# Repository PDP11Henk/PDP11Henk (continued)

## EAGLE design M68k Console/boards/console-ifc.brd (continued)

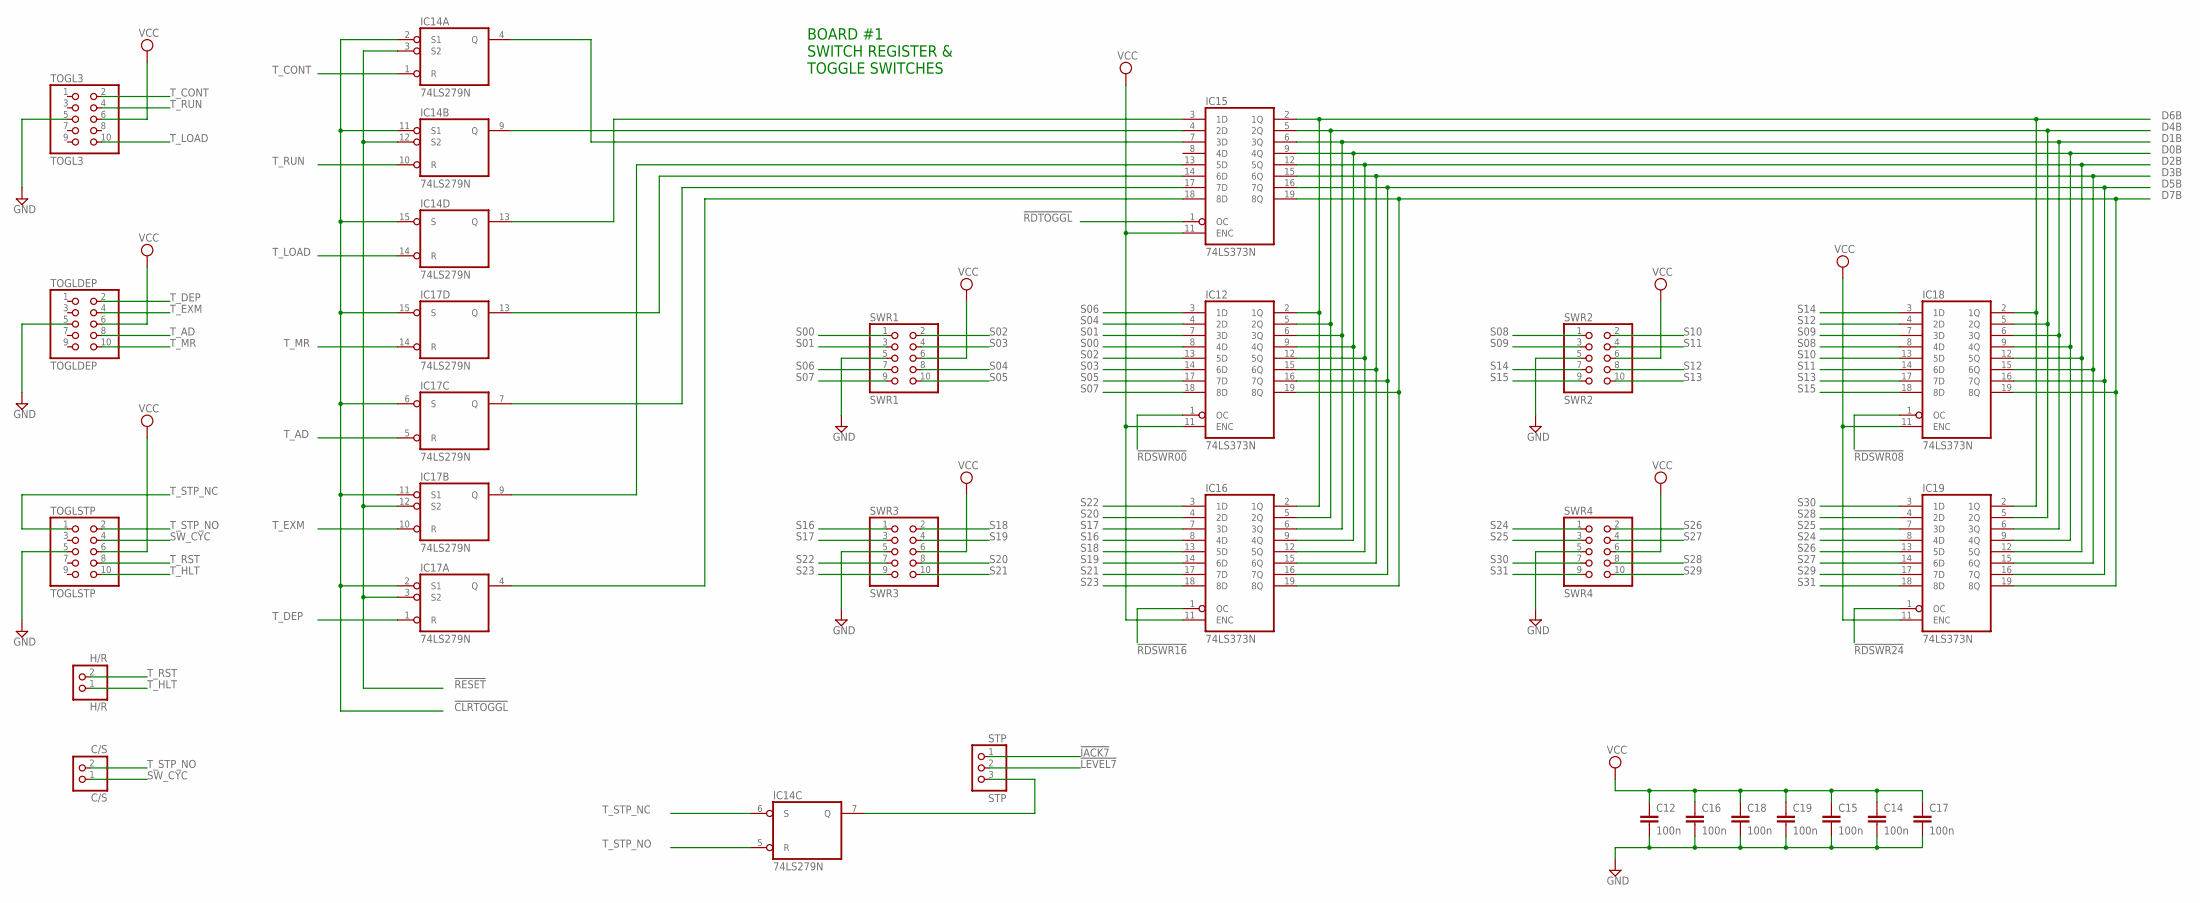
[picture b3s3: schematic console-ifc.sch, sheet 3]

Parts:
C12, C14, C15, C16, C17, C18, C19: 100n; C025-024X044
C/S: C/S; 1X02
H/R: H/R; 1X02
IC12, IC15, IC16, IC18, IC19: 74LS373N; DIL20
IC14, IC17: 74LS279N; DIL16
STP: STP; 1X03
SWR1: SWR1; 2X05
SWR2: SWR2; 2X05
SWR3: SWR3; 2X05
SWR4: SWR4; 2X05
TOGL3: TOGL3; 2X05
TOGLDEP: TOGLDEP; 2X05
TOGLSTP: TOGLSTP; 2X05

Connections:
!CLRTOGGL: IC14.2 (S1), IC14.11 (S1), IC14.15 (S), IC17.2 (S1), IC17.6 (S), IC17.11 (S1), IC17.15 (S); also elsewhere on the board
!IACK7: STP.1; also elsewhere on the board
!LEVEL7: STP.2; also elsewhere on the board
!RDSWR00: IC12.1 (OC); also elsewhere on the board
!RDSWR08: IC18.1 (OC); also elsewhere on the board
!RDSWR16: IC16.1 (OC); also elsewhere on the board
!RDSWR24: IC19.1 (OC); also elsewhere on the board
!RDTOGGL: IC15.1 (OC); also elsewhere on the board
!RESET: IC14.3 (S2), IC14.12 (S2), IC17.3 (S2), IC17.12 (S2); also elsewhere on the board
D0B: IC12.9 (4Q), IC15.9 (4Q), IC16.9 (4Q), IC18.9 (4Q), IC19.9 (4Q); also elsewhere on the board
D1B: IC12.6 (3Q), IC15.6 (3Q), IC16.6 (3Q), IC18.6 (3Q), IC19.6 (3Q); also elsewhere on the board
D2B: IC12.12 (5Q), IC15.12 (5Q), IC16.12 (5Q), IC18.12 (5Q), IC19.12 (5Q); also elsewhere on the board
D3B: IC12.15 (6Q), IC15.15 (6Q), IC16.15 (6Q), IC18.15 (6Q), IC19.15 (6Q); also elsewhere on the board
D4B: IC12.5 (2Q), IC15.5 (2Q), IC16.5 (2Q), IC18.5 (2Q), IC19.5 (2Q); also elsewhere on the board
D5B: IC12.16 (7Q), IC15.16 (7Q), IC16.16 (7Q), IC18.16 (7Q), IC19.16 (7Q); also elsewhere on the board
D6B: IC12.2 (1Q), IC15.2 (1Q), IC16.2 (1Q), IC18.2 (1Q), IC19.2 (1Q); also elsewhere on the board
D7B: IC12.19 (8Q), IC15.19 (8Q), IC16.19 (8Q), IC18.19 (8Q), IC19.19 (8Q); also elsewhere on the board
GND: C12.2, C14.2, C15.2, C16.2, C17.2, C18.2, C19.2, IC12.10 (GND), IC14.8 (GND), IC15.10 (GND), IC16.10 (GND), IC17.8 (GND), IC18.10 (GND), IC19.10 (GND), SWR1.5, SWR2.5, SWR3.5, SWR4.5, TOGL3.5, TOGLDEP.5, TOGLSTP.5; also elsewhere on the board
unnamed: IC15.18 (8D), IC17.4 (Q)
unnamed: IC14.7 (Q), STP.3
unnamed: IC15.17 (7D), IC17.7 (Q)
unnamed: IC15.14 (6D), IC17.13 (Q)
unnamed: IC15.13 (5D), IC17.9 (Q)
unnamed: IC14.13 (Q), IC15.3 (1D)
unnamed: IC14.9 (Q), IC15.4 (2D)
unnamed: IC14.4 (Q), IC15.7 (3D)
S00: IC12.8 (4D), SWR1.1
S01: IC12.7 (3D), SWR1.3
S02: IC12.13 (5D), SWR1.2
S03: IC12.14 (6D), SWR1.4
S04: IC12.4 (2D), SWR1.8
S05: IC12.17 (7D), SWR1.10
S06: IC12.3 (1D), SWR1.7
S07: IC12.18 (8D), SWR1.9
S08: IC18.8 (4D), SWR2.1
S09: IC18.7 (3D), SWR2.3
S10: IC18.13 (5D), SWR2.2
S11: IC18.14 (6D), SWR2.4
S12: IC18.4 (2D), SWR2.8
S13: IC18.17 (7D), SWR2.10
S14: IC18.3 (1D), SWR2.7
S15: IC18.18 (8D), SWR2.9
S16: IC16.8 (4D), SWR3.1
S17: IC16.7 (3D), SWR3.3
S18: IC16.13 (5D), SWR3.2
S19: IC16.14 (6D), SWR3.4
S20: IC16.4 (2D), SWR3.8
S21: IC16.17 (7D), SWR3.10
S22: IC16.3 (1D), SWR3.7
S23: IC16.18 (8D), SWR3.9
S24: IC19.8 (4D), SWR4.1
S25: IC19.7 (3D), SWR4.3
S26: IC19.13 (5D), SWR4.2
S27: IC19.14 (6D), SWR4.4
S28: IC19.4 (2D), SWR4.8
S29: IC19.17 (7D), SWR4.10
S30: IC19.3 (1D), SWR4.7
S31: IC19.18 (8D), SWR4.9
SW_CYC: C/S.1, TOGLSTP.4
T_AD: IC17.5 (R), TOGLDEP.8
T_CONT: IC14.1 (R), TOGL3.2
T_DEP: IC17.1 (R), TOGLDEP.2
T_EXM: IC17.10 (R), TOGLDEP.4
T_HLT: H/R.1, TOGLSTP.10
T_LOAD: IC14.14 (R), TOGL3.10
T_MR: IC17.14 (R), TOGLDEP.10
T_RST: H/R.2, TOGLSTP.8
T_RUN: IC14.10 (R), TOGL3.4
T_STP_NC: IC14.6 (S), TOGLSTP.1
T_STP_NO: C/S.2, IC14.5 (R), TOGLSTP.2
VCC: C12.1, C14.1, C15.1, C16.1, C17.1, C18.1, C19.1, IC12.11 (ENC), IC12.20 (VCC), IC14.16 (VCC), IC15.11 (ENC), IC15.20 (VCC), IC16.11 (ENC), IC16.20 (VCC), IC17.16 (VCC), IC18.11 (ENC), IC18.20 (VCC), IC19.11 (ENC), IC19.20 (VCC), SWR1.6, SWR2.6, SWR3.6, SWR4.6, TOGL3.6, TOGLDEP.6, TOGLSTP.6; also elsewhere on the board

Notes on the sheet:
BOARD #1 SWITCH REGISTER & TOGGLE SWITCHES

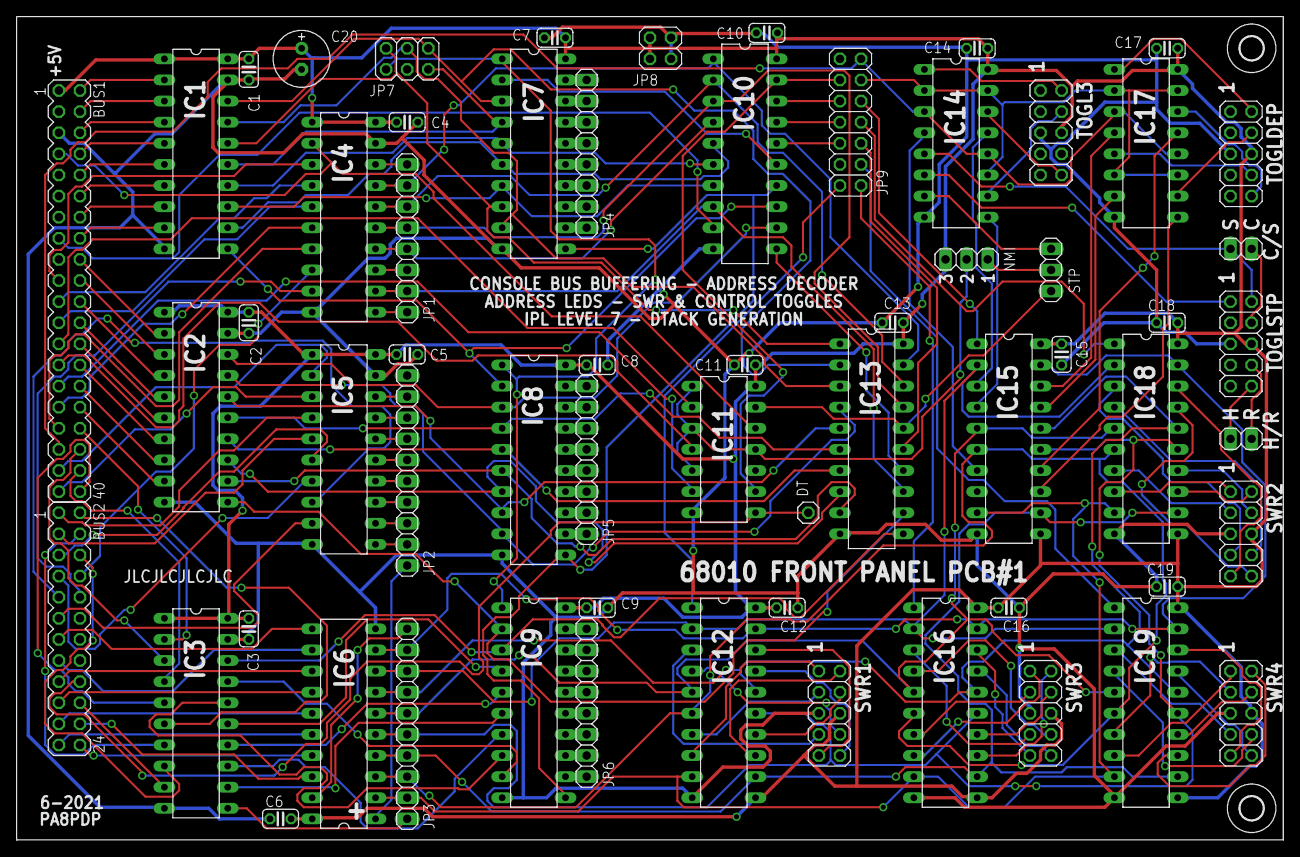
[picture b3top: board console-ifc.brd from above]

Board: 2 copper layers, 152.4 x 99.1 mm, 64 parts (0 on the bottom side), 200 nets.

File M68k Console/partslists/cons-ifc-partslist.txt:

Partlist

Exported from console-ifc.sch at 14-6-2021 21:02

EAGLE Version 7.6.0 Copyright (c) 1988-2016 CadSoft

Assembly variant: 

Part     Value          Device          Package      Library  Sheet

BUS1     BUS1           MA20-2          MA20-2       con-lstb 1
BUS2     BUS2           MA12-2          MA12-2       con-lstb 1
C/S      C/S            PINHD-1X2       1X02         pinhead  3
C1       100n           C-EU025-024X044 C025-024X044 rcl      1
C2       100n           C-EU025-024X044 C025-024X044 rcl      1
C3       100n           C-EU025-024X044 C025-024X044 rcl      1
C4       100n           C-EU025-024X044 C025-024X044 rcl      1
C5       100n           C-EU025-024X044 C025-024X044 rcl      1
C6       100n           C-EU025-024X044 C025-024X044 rcl      1
C7       100n           C-EU025-024X044 C025-024X044 rcl      2
C8       100n           C-EU025-024X044 C025-024X044 rcl      2
C9       100n           C-EU025-024X044 C025-024X044 rcl      2
C10      220n           C-EU025-024X044 C025-024X044 rcl      2
C11      100n           C-EU025-024X044 C025-024X044 rcl      2
C12      100n           C-EU025-024X044 C025-024X044 rcl      3
C13      220n           C-EU025-024X044 C025-024X044 rcl      2
C14      100n           C-EU025-024X044 C025-024X044 rcl      3
C15      100n           C-EU025-024X044 C025-024X044 rcl      3
C16      100n           C-EU025-024X044 C025-024X044 rcl      3
C17      100n           C-EU025-024X044 C025-024X044 rcl      3
C18      100n           C-EU025-024X044 C025-024X044 rcl      3
C19      100n           C-EU025-024X044 C025-024X044 rcl      3
C20      470µF          CPOL-EUE2.5-7   E2,5-7       rcl      1
DT       DT             PINHD-1X1       1X01         pinhead  2
H/R      H/R            PINHD-1X2       1X02         pinhead  3
IC1      74LS245N       74LS245N        DIL20        74xx-eu  1
IC2      74LS245N       74LS245N        DIL20        74xx-eu  1
IC3      74LS245N       74LS245N        DIL20        74xx-eu  1
IC4      74LS245N       74LS245N        DIL20        74xx-eu  1
IC5      74LS245N       74LS245N        DIL20        74xx-eu  1
IC6      74LS245N       74LS245N        DIL20        74xx-eu  1
IC7      74HCT574N      74HCT574N       DIL20        74xx-eu  2
IC8      74HCT574N      74HCT574N       DIL20        74xx-eu  2
IC9      74HCT574N      74HCT574N       DIL20        74xx-eu  2
IC10     ATF16V8BP3     ATF16V8BP3      DIL20        atmel    2
IC11     74LS07N        74LS07N         DIL14        74xx-eu  2
IC12     74LS373N       74LS373N        DIL20        74xx-eu  3
IC13     ATF16V8BP3     ATF16V8BP3      DIL20        atmel    2
IC14     74LS279N       74LS279N        DIL16        74xx-eu  3
IC15     74LS373N       74LS373N        DIL20        74xx-eu  3
IC16     74LS373N       74LS373N        DIL20        74xx-eu  3
IC17     74LS279N       74LS279N        DIL16        74xx-eu  3
IC18     74LS373N       74LS373N        DIL20        74xx-eu  3
IC19     74LS373N       74LS373N        DIL20        74xx-eu  3
JP1      JP1            PINHD-1X8       1X08         pinhead  1
JP2      JP2            PINHD-1X10      1X10         pinhead  1
JP3      JP3            PINHD-1X10      1X10         pinhead  1
JP4      JP4            PINHD-1X8       1X08         pinhead  2
JP5      JP5            PINHD-1X8       1X08         pinhead  2
JP6      JP6            PINHD-1X8       1X08         pinhead  2
JP7      JP7            PINHD-2X3       2X03         pinhead  1
JP8      JP8            PINHD-2X2       2X02         pinhead  1
JP9      JP9            PINHD-2X7       2X07         pinhead  2
NMI      NMI            PINHD-1X3       1X03         pinhead  2
STP      STP            PINHD-1X3       1X03         pinhead  3
SWR1     SWR1           PINHD-2X5       2X05         pinhead  3
SWR2     SWR2           PINHD-2X5       2X05         pinhead  3
SWR3     SWR3           PINHD-2X5       2X05         pinhead  3
SWR4     SWR4           PINHD-2X5       2X05         pinhead  3
TOGL3    TOGL3          PINHD-2X5       2X05         pinhead  3
TOGLDEP  TOGLDEP        PINHD-2X5       2X05         pinhead  3
TOGLSTP  TOGLSTP        PINHD-2X5       2X05         pinhead  3

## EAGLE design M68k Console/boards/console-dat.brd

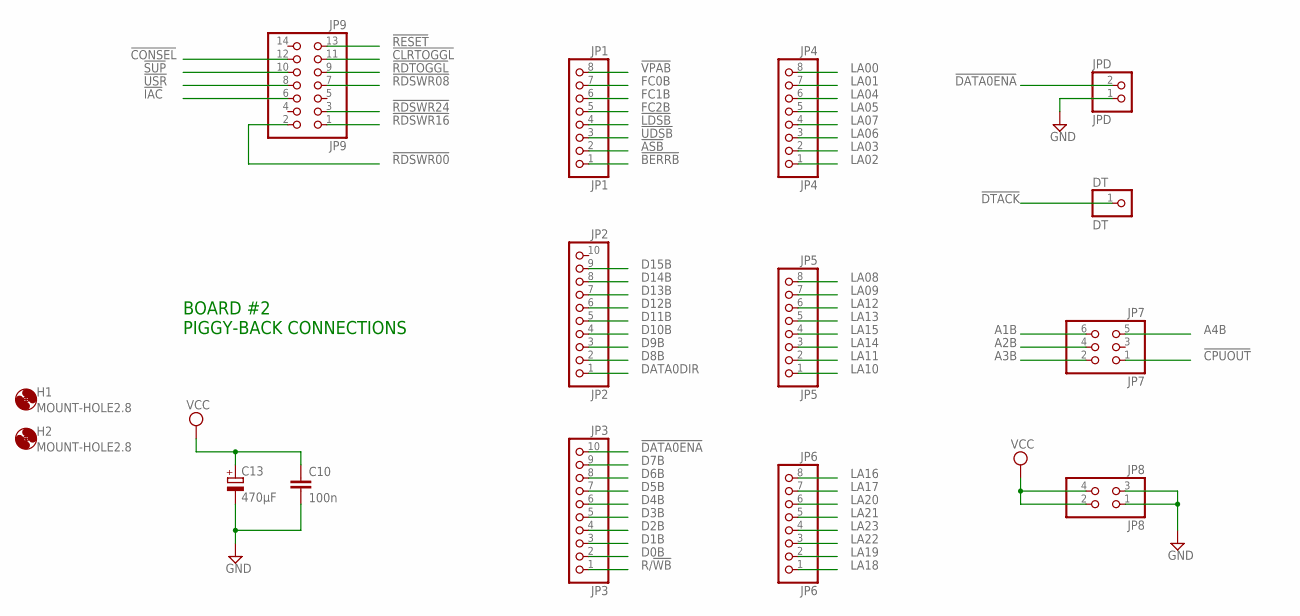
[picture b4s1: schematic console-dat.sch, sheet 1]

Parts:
C10: 100n; C025-024X044
C13: 470µF; E2,5-7
DT: DT; 1X01
H1, H2: MOUNT-HOLE2.8; 2,8
JP1: JP1; 1X08
JP2: JP2; 1X10
JP3: JP3; 1X10
JP4: JP4; 1X08
JP5: JP5; 1X08
JP6: JP6; 1X08
JP7: JP7; 2X03
JP8: JP8; 2X02
JP9: JP9; 2X07
JPD: JPD; 1X02

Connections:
!ASB: JP1.2
!BERRB: JP1.1
!CLRTOGGL: JP9.11; also elsewhere on the board
!CONSEL: JP9.12; also elsewhere on the board
!CPUOUT: JP7.1; also elsewhere on the board
!DATA0ENA: JP3.10, JPD.2
!DTACK: DT.1; also elsewhere on the board
!IAC: JP9.6; also elsewhere on the board
!LDSB: JP1.4; also elsewhere on the board
!RDSWR00: JP9.2; also elsewhere on the board
!RDSWR08: JP9.7; also elsewhere on the board
!RDSWR16: JP9.1; also elsewhere on the board
!RDSWR24: JP9.3; also elsewhere on the board
!RDTOGGL: JP9.9; also elsewhere on the board
!RESET: JP9.13; also elsewhere on the board
!SUP: JP9.10; also elsewhere on the board
!UDSB: JP1.3; also elsewhere on the board
!USR: JP9.8; also elsewhere on the board
!VPAB: JP1.8; also elsewhere on the board
A1B: JP7.6; also elsewhere on the board
A2B: JP7.4; also elsewhere on the board
A3B: JP7.2; also elsewhere on the board
A4B: JP7.5; also elsewhere on the board
D0B: JP3.2; also elsewhere on the board
D1B: JP3.3; also elsewhere on the board
D2B: JP3.4; also elsewhere on the board
D3B: JP3.5; also elsewhere on the board
D4B: JP3.6; also elsewhere on the board
D5B: JP3.7; also elsewhere on the board
D6B: JP3.8; also elsewhere on the board
D7B: JP3.9; also elsewhere on the board
D8B: JP2.2; also elsewhere on the board
D9B: JP2.3; also elsewhere on the board
D10B: JP2.4; also elsewhere on the board
D11B: JP2.5; also elsewhere on the board
D12B: JP2.6; also elsewhere on the board
D13B: JP2.7; also elsewhere on the board
D14B: JP2.8; also elsewhere on the board
D15B: JP2.9; also elsewhere on the board
DATA0DIR: JP2.1; also elsewhere on the board
FC0B: JP1.7; also elsewhere on the board
FC1B: JP1.6; also elsewhere on the board
FC2B: JP1.5; also elsewhere on the board
GND: C10.2, C13.-, JP8.1, JP8.3, JPD.1; also elsewhere on the board
LA00: JP4.8; also elsewhere on the board
LA01: JP4.7; also elsewhere on the board
LA02: JP4.1; also elsewhere on the board
LA03: JP4.2; also elsewhere on the board
LA04: JP4.6; also elsewhere on the board
LA05: JP4.5; also elsewhere on the board
LA06: JP4.3; also elsewhere on the board
LA07: JP4.4; also elsewhere on the board
LA08: JP5.8; also elsewhere on the board
LA09: JP5.7; also elsewhere on the board
LA10: JP5.1; also elsewhere on the board
LA11: JP5.2; also elsewhere on the board
LA12: JP5.6; also elsewhere on the board
LA13: JP5.5; also elsewhere on the board
LA14: JP5.3; also elsewhere on the board
LA15: JP5.4; also elsewhere on the board
LA16: JP6.8; also elsewhere on the board
LA17: JP6.7; also elsewhere on the board
LA18: JP6.1; also elsewhere on the board
LA19: JP6.2; also elsewhere on the board
LA20: JP6.6; also elsewhere on the board
LA21: JP6.5; also elsewhere on the board
LA22: JP6.3; also elsewhere on the board
LA23: JP6.4; also elsewhere on the board
R/!WB: JP3.1; also elsewhere on the board
VCC: C10.1, C13.+, JP8.2, JP8.4; also elsewhere on the board

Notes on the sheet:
BOARD #2 PIGGY-BACK CONNECTIONS

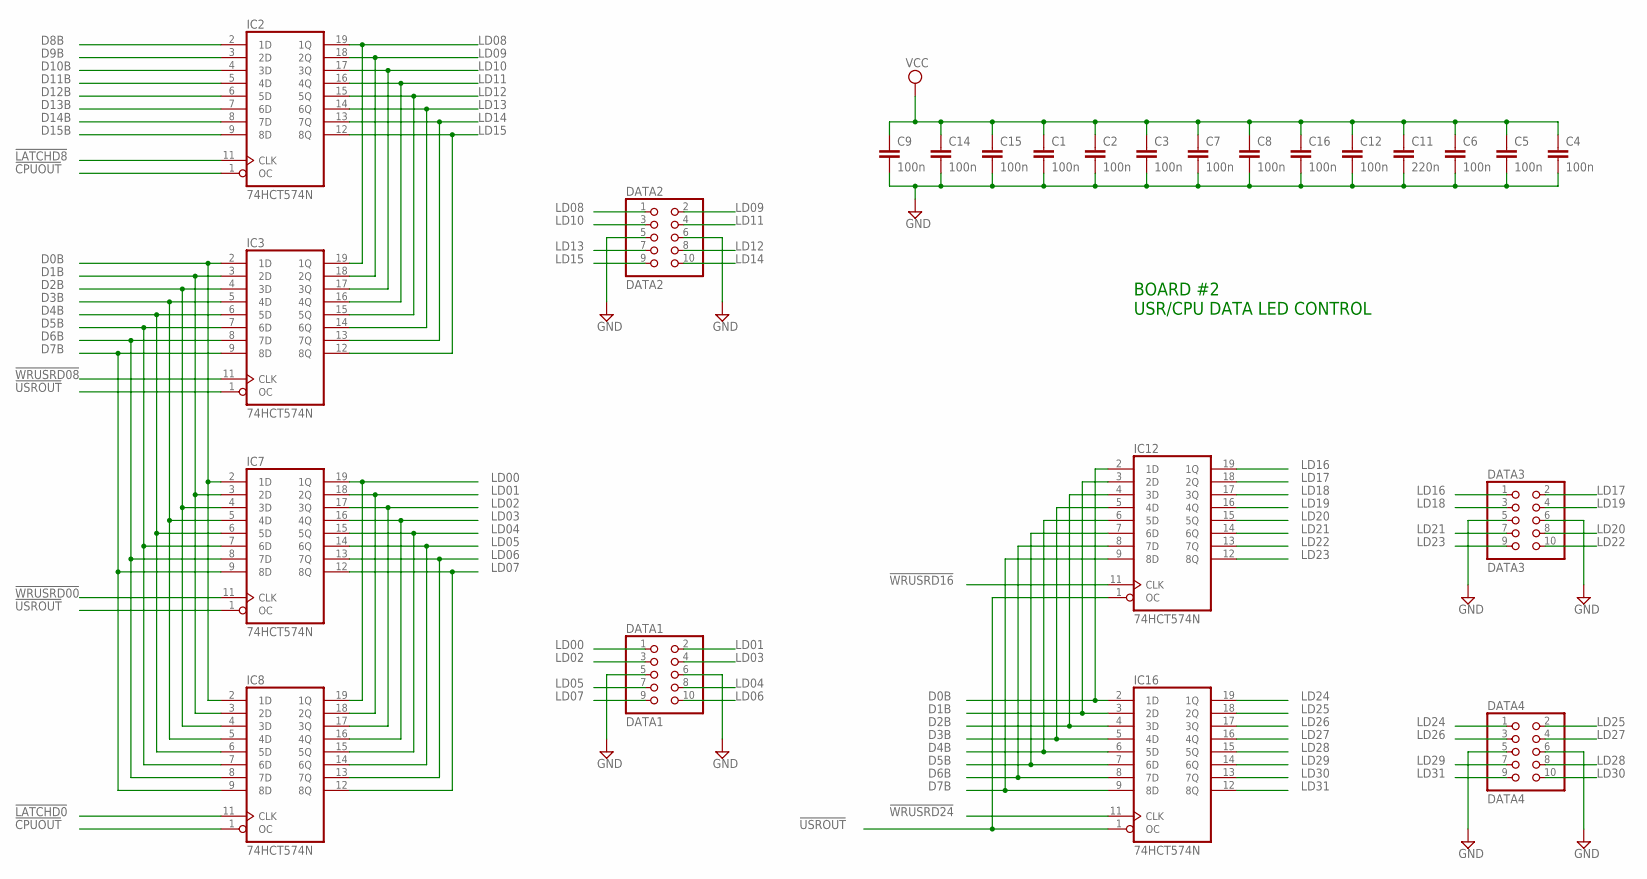
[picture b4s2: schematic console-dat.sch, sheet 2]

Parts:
C1, C2, C3, C4, C5, C6, C7, C8, C9, C12, C14, C15, C16: 100n; C025-024X044
C11: 220n; C025-024X044
DATA1: DATA1; 2X05
DATA2: DATA2; 2X05
DATA3: DATA3; 2X05
DATA4: DATA4; 2X05
IC2, IC3, IC7, IC8, IC12, IC16: 74HCT574N; DIL20

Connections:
!CPUOUT: IC2.1 (OC), IC8.1 (OC); also elsewhere on the board
!LATCHD0: IC8.11 (CLK); also elsewhere on the board
!LATCHD8: IC2.11 (CLK); also elsewhere on the board
!USROUT: IC3.1 (OC), IC7.1 (OC), IC12.1 (OC), IC16.1 (OC); also elsewhere on the board
!WRUSRD00: IC7.11 (CLK); also elsewhere on the board
!WRUSRD08: IC3.11 (CLK); also elsewhere on the board
!WRUSRD16: IC12.11 (CLK); also elsewhere on the board
!WRUSRD24: IC16.11 (CLK); also elsewhere on the board
D0B: IC3.2 (1D), IC7.2 (1D), IC8.2 (1D), IC12.2 (1D), IC16.2 (1D); also elsewhere on the board
D1B: IC3.3 (2D), IC7.3 (2D), IC8.3 (2D), IC12.3 (2D), IC16.3 (2D); also elsewhere on the board
D2B: IC3.4 (3D), IC7.4 (3D), IC8.4 (3D), IC12.4 (3D), IC16.4 (3D); also elsewhere on the board
D3B: IC3.5 (4D), IC7.5 (4D), IC8.5 (4D), IC12.5 (4D), IC16.5 (4D); also elsewhere on the board
D4B: IC3.6 (5D), IC7.6 (5D), IC8.6 (5D), IC12.6 (5D), IC16.6 (5D); also elsewhere on the board
D5B: IC3.7 (6D), IC7.7 (6D), IC8.7 (6D), IC12.7 (6D), IC16.7 (6D); also elsewhere on the board
D6B: IC3.8 (7D), IC7.8 (7D), IC8.8 (7D), IC12.8 (7D), IC16.8 (7D); also elsewhere on the board
D7B: IC3.9 (8D), IC7.9 (8D), IC8.9 (8D), IC12.9 (8D), IC16.9 (8D); also elsewhere on the board
D8B: IC2.2 (1D); also elsewhere on the board
D9B: IC2.3 (2D); also elsewhere on the board
D10B: IC2.4 (3D); also elsewhere on the board
D11B: IC2.5 (4D); also elsewhere on the board
D12B: IC2.6 (5D); also elsewhere on the board
D13B: IC2.7 (6D); also elsewhere on the board
D14B: IC2.8 (7D); also elsewhere on the board
D15B: IC2.9 (8D); also elsewhere on the board
GND: C1.2, C2.2, C3.2, C4.2, C5.2, C6.2, C7.2, C8.2, C9.2, C11.2, C12.2, C14.2, C15.2, C16.2, DATA1.5, DATA1.6, DATA2.5, DATA2.6, DATA3.5, DATA3.6, DATA4.5, DATA4.6, IC2.10 (GND), IC3.10 (GND), IC7.10 (GND), IC8.10 (GND), IC12.10 (GND), IC16.10 (GND); also elsewhere on the board
LD00: DATA1.1, IC7.19 (1Q), IC8.19 (1Q)
LD01: DATA1.2, IC7.18 (2Q), IC8.18 (2Q)
LD02: DATA1.3, IC7.17 (3Q), IC8.17 (3Q)
LD03: DATA1.4, IC7.16 (4Q), IC8.16 (4Q)
LD04: DATA1.8, IC7.15 (5Q), IC8.15 (5Q)
LD05: DATA1.7, IC7.14 (6Q), IC8.14 (6Q)
LD06: DATA1.10, IC7.13 (7Q), IC8.13 (7Q)
LD07: DATA1.9, IC7.12 (8Q), IC8.12 (8Q)
LD08: DATA2.1, IC2.19 (1Q), IC3.19 (1Q)
LD09: DATA2.2, IC2.18 (2Q), IC3.18 (2Q)
LD10: DATA2.3, IC2.17 (3Q), IC3.17 (3Q)
LD11: DATA2.4, IC2.16 (4Q), IC3.16 (4Q)
LD12: DATA2.8, IC2.15 (5Q), IC3.15 (5Q)
LD13: DATA2.7, IC2.14 (6Q), IC3.14 (6Q)
LD14: DATA2.10, IC2.13 (7Q), IC3.13 (7Q)
LD15: DATA2.9, IC2.12 (8Q), IC3.12 (8Q)
LD16: DATA3.1, IC12.19 (1Q)
LD17: DATA3.2, IC12.18 (2Q)
LD18: DATA3.3, IC12.17 (3Q)
LD19: DATA3.4, IC12.16 (4Q)
LD20: DATA3.8, IC12.15 (5Q)
LD21: DATA3.7, IC12.14 (6Q)
LD22: DATA3.10, IC12.13 (7Q)
LD23: DATA3.9, IC12.12 (8Q)
LD24: DATA4.1, IC16.19 (1Q)
LD25: DATA4.2, IC16.18 (2Q)
LD26: DATA4.3, IC16.17 (3Q)
LD27: DATA4.4, IC16.16 (4Q)
LD28: DATA4.8, IC16.15 (5Q)
LD29: DATA4.7, IC16.14 (6Q)
LD30: DATA4.10, IC16.13 (7Q)
LD31: DATA4.9, IC16.12 (8Q)
VCC: C1.1, C2.1, C3.1, C4.1, C5.1, C6.1, C7.1, C8.1, C9.1, C11.1, C12.1, C14.1, C15.1, C16.1, IC2.20 (VCC), IC3.20 (VCC), IC7.20 (VCC), IC8.20 (VCC), IC12.20 (VCC), IC16.20 (VCC); also elsewhere on the board

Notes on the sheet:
BOARD #2 USR/CPU DATA LED CONTROL

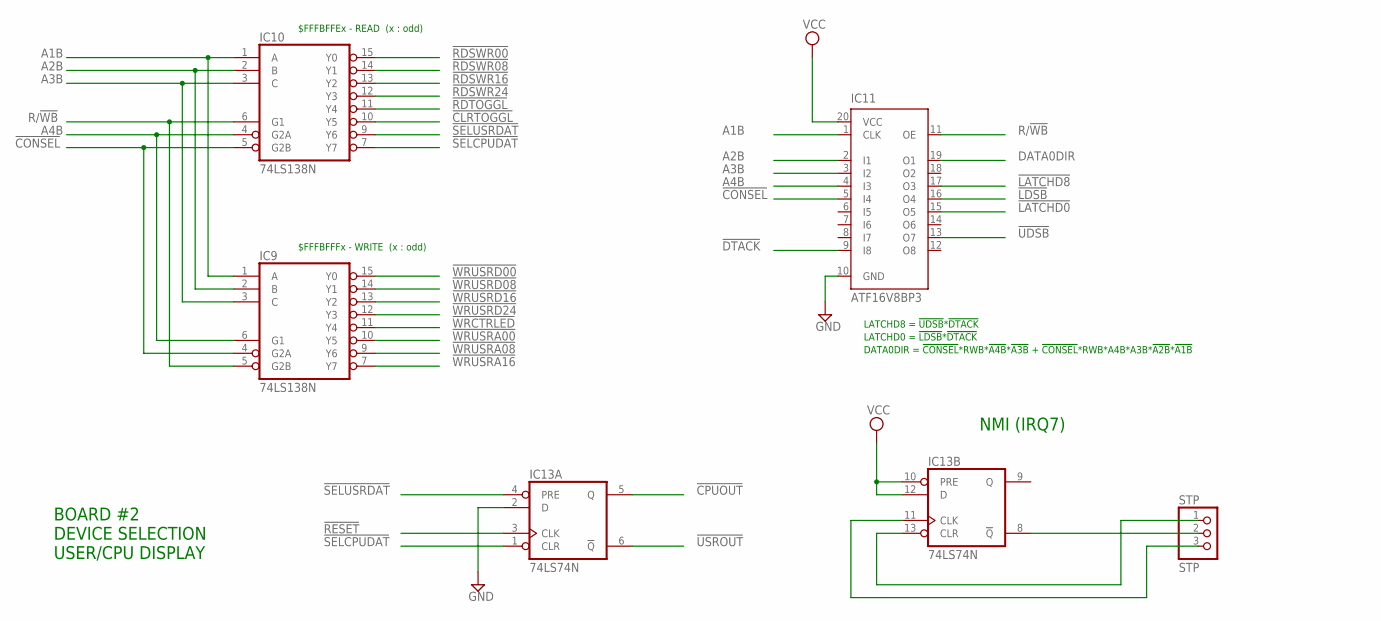
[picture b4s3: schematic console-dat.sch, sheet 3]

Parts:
IC9, IC10: 74LS138N; DIL16
IC11: ATF16V8BP3; DIL20
IC13: 74LS74N; DIL14
STP: STP; 1X03

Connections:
!CLRTOGGL: IC10.10 (Y5); also elsewhere on the board
!CONSEL: IC9.4 (G2A), IC10.5 (G2B), IC11.5 (I4); also elsewhere on the board
!CPUOUT: IC13.5 (Q); also elsewhere on the board
!DTACK: IC11.9 (I8); also elsewhere on the board
!LATCHD0: IC11.15 (O5); also elsewhere on the board
!LATCHD8: IC11.17 (O3); also elsewhere on the board
!LDSB: IC11.16 (O4); also elsewhere on the board
!RDSWR00: IC10.15 (Y0); also elsewhere on the board
!RDSWR08: IC10.14 (Y1); also elsewhere on the board
!RDSWR16: IC10.13 (Y2); also elsewhere on the board
!RDSWR24: IC10.12 (Y3); also elsewhere on the board
!RDTOGGL: IC10.11 (Y4); also elsewhere on the board
!RESET: IC13.3 (CLK); also elsewhere on the board
!SELCPUDAT: IC10.7 (Y7), IC13.1 (CLR)
!SELUSRDAT: IC10.9 (Y6), IC13.4 (PRE)
!UDSB: IC11.13 (O7); also elsewhere on the board
!USROUT: IC13.6 (!Q); also elsewhere on the board
!WRCTRLED: IC9.11 (Y4); also elsewhere on the board
!WRUSRA00: IC9.10 (Y5); also elsewhere on the board
!WRUSRA08: IC9.9 (Y6); also elsewhere on the board
!WRUSRA16: IC9.7 (Y7); also elsewhere on the board
!WRUSRD00: IC9.15 (Y0); also elsewhere on the board
!WRUSRD08: IC9.14 (Y1); also elsewhere on the board
!WRUSRD16: IC9.13 (Y2); also elsewhere on the board
!WRUSRD24: IC9.12 (Y3); also elsewhere on the board
A1B: IC9.1 (A), IC10.1 (A), IC11.1 (CLK); also elsewhere on the board
A2B: IC9.2 (B), IC10.2 (B), IC11.2 (I1); also elsewhere on the board
A3B: IC9.3 (C), IC10.3 (C), IC11.3 (I2); also elsewhere on the board
A4B: IC9.6 (G1), IC10.4 (G2A), IC11.4 (I3); also elsewhere on the board
DATA0DIR: IC11.19 (O1); also elsewhere on the board
GND: IC9.8 (GND), IC10.8 (GND), IC11.10 (GND), IC13.2 (D), IC13.7 (GND); also elsewhere on the board
unnamed: IC13.11 (CLK), STP.3
unnamed: IC13.8 (!Q), STP.2
unnamed: IC13.13 (CLR), STP.1
R/!WB: IC9.5 (G2B), IC10.6 (G1), IC11.11 (OE); also elsewhere on the board
VCC: IC9.16 (VCC), IC10.16 (VCC), IC11.20 (VCC), IC13.10 (PRE), IC13.12 (D), IC13.14 (VCC); also elsewhere on the board

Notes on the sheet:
BOARD #2 DEVICE SELECTION USER/CPU DISPLAY
$FFFBFFEx - READ (x : odd)
$FFFBFFFx - WRITE (x : odd)
NMI (IRQ7)
LATCHD8 = !UDSB!*!DTACK
LATCHD0 = !LDSB!*!DTACK
DATA0DIR = !CONSEL!*RWB*!A4B!*!A3B! + !CONSEL!*RWB*A4B*A3B*!A2B!*!A1B!

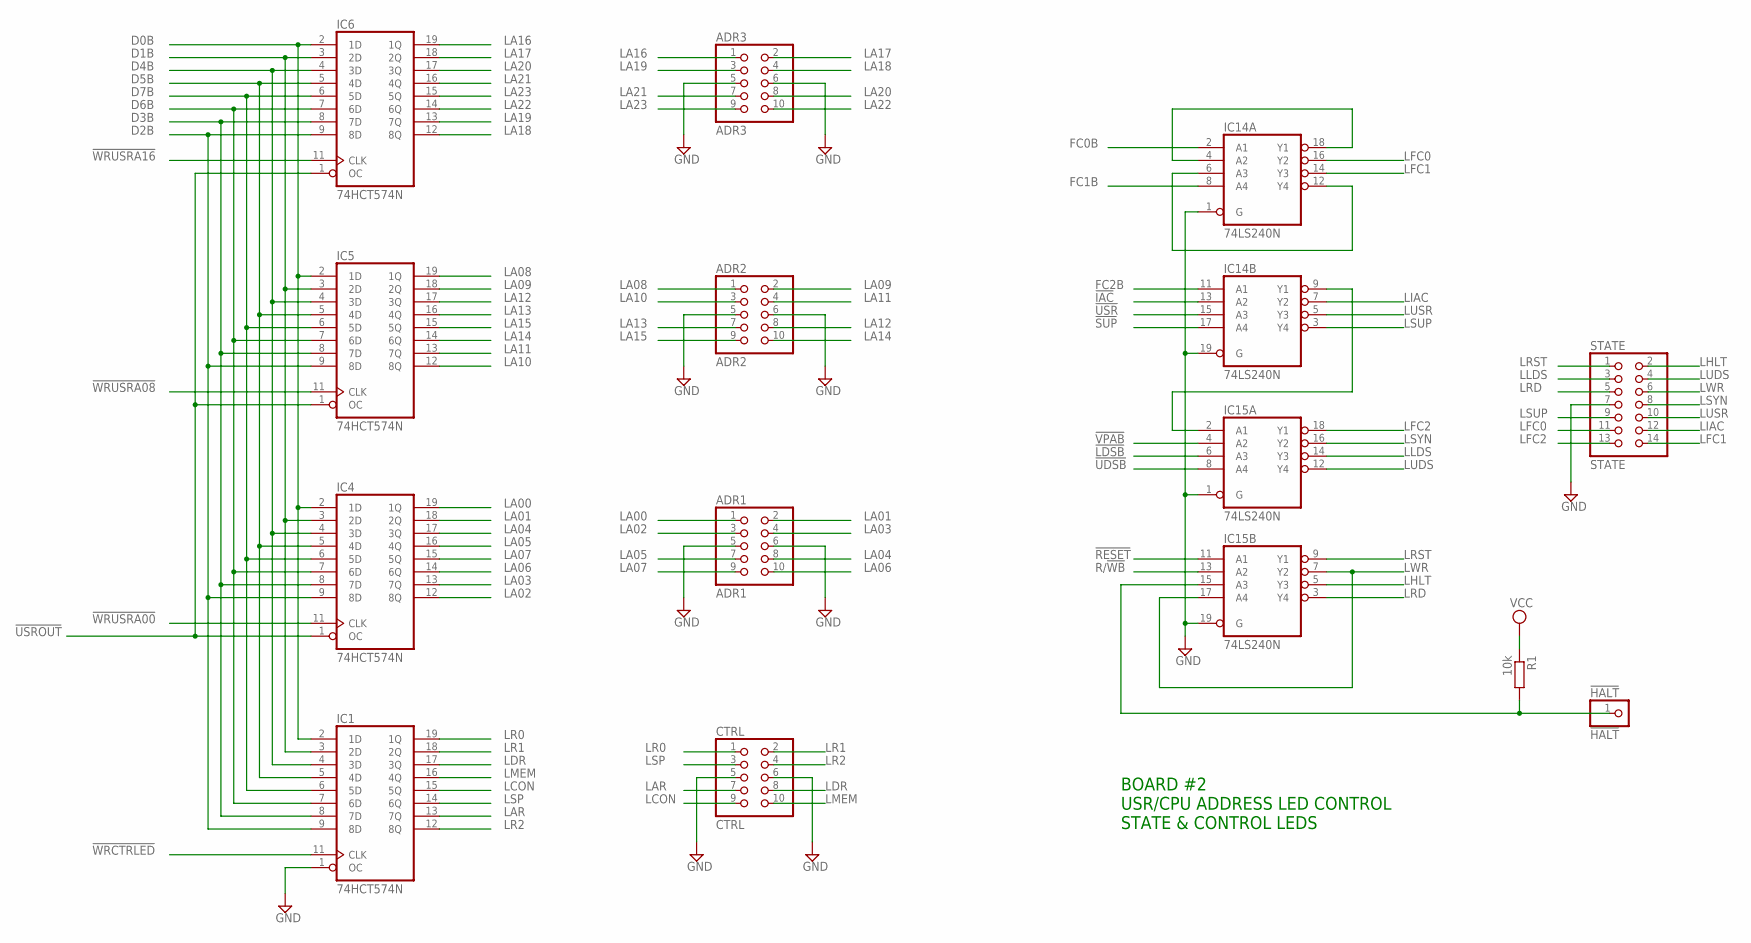
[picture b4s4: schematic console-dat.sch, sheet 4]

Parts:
!HALT: !HALT; 1X01
ADR1: ADR1; 2X05
ADR2: ADR2; 2X05
ADR3: ADR3; 2X05
CTRL: CTRL; 2X05
IC1, IC4, IC5, IC6: 74HCT574N; DIL20
IC14, IC15: 74LS240N; DIL20
R1: 10k; 0204/7
STATE: STATE; 2X07

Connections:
!IAC: IC14.13 (A2); also elsewhere on the board
!LDSB: IC15.6 (A3); also elsewhere on the board
!RESET: IC15.11 (A1); also elsewhere on the board
!SUP: IC14.17 (A4); also elsewhere on the board
!UDSB: IC15.8 (A4); also elsewhere on the board
!USR: IC14.15 (A3); also elsewhere on the board
!USROUT: IC4.1 (OC), IC5.1 (OC), IC6.1 (OC); also elsewhere on the board
!VPAB: IC15.4 (A2); also elsewhere on the board
!WRCTRLED: IC1.11 (CLK); also elsewhere on the board
!WRUSRA00: IC4.11 (CLK); also elsewhere on the board
!WRUSRA08: IC5.11 (CLK); also elsewhere on the board
!WRUSRA16: IC6.11 (CLK); also elsewhere on the board
D0B: IC1.2 (1D), IC4.2 (1D), IC5.2 (1D), IC6.2 (1D); also elsewhere on the board
D1B: IC1.3 (2D), IC4.3 (2D), IC5.3 (2D), IC6.3 (2D); also elsewhere on the board
D2B: IC1.9 (8D), IC4.9 (8D), IC5.9 (8D), IC6.9 (8D); also elsewhere on the board
D3B: IC1.8 (7D), IC4.8 (7D), IC5.8 (7D), IC6.8 (7D); also elsewhere on the board
D4B: IC1.4 (3D), IC4.4 (3D), IC5.4 (3D), IC6.4 (3D); also elsewhere on the board
D5B: IC1.5 (4D), IC4.5 (4D), IC5.5 (4D), IC6.5 (4D); also elsewhere on the board
D6B: IC1.7 (6D), IC4.7 (6D), IC5.7 (6D), IC6.7 (6D); also elsewhere on the board
D7B: IC1.6 (5D), IC4.6 (5D), IC5.6 (5D), IC6.6 (5D); also elsewhere on the board
FC0B: IC14.2 (A1); also elsewhere on the board
FC1B: IC14.8 (A4); also elsewhere on the board
FC2B: IC14.11 (A1); also elsewhere on the board
GND: ADR1.5, ADR1.6, ADR2.5, ADR2.6, ADR3.5, ADR3.6, CTRL.5, CTRL.6, IC1.1 (OC), IC1.10 (GND), IC4.10 (GND), IC5.10 (GND), IC6.10 (GND), IC14.1 (G), IC14.10 (GND), IC14.19 (G), IC15.1 (G), IC15.10 (GND), IC15.19 (G), STATE.7; also elsewhere on the board
LA00: ADR1.1, IC4.19 (1Q); also elsewhere on the board
LA01: ADR1.2, IC4.18 (2Q); also elsewhere on the board
LA02: ADR1.3, IC4.12 (8Q); also elsewhere on the board
LA03: ADR1.4, IC4.13 (7Q); also elsewhere on the board
LA04: ADR1.8, IC4.17 (3Q); also elsewhere on the board
LA05: ADR1.7, IC4.16 (4Q); also elsewhere on the board
LA06: ADR1.10, IC4.14 (6Q); also elsewhere on the board
LA07: ADR1.9, IC4.15 (5Q); also elsewhere on the board
LA08: ADR2.1, IC5.19 (1Q); also elsewhere on the board
LA09: ADR2.2, IC5.18 (2Q); also elsewhere on the board
LA10: ADR2.3, IC5.12 (8Q); also elsewhere on the board
LA11: ADR2.4, IC5.13 (7Q); also elsewhere on the board
LA12: ADR2.8, IC5.17 (3Q); also elsewhere on the board
LA13: ADR2.7, IC5.16 (4Q); also elsewhere on the board
LA14: ADR2.10, IC5.14 (6Q); also elsewhere on the board
LA15: ADR2.9, IC5.15 (5Q); also elsewhere on the board
LA16: ADR3.1, IC6.19 (1Q); also elsewhere on the board
LA17: ADR3.2, IC6.18 (2Q); also elsewhere on the board
LA18: ADR3.4, IC6.12 (8Q); also elsewhere on the board
LA19: ADR3.3, IC6.13 (7Q); also elsewhere on the board
LA20: ADR3.8, IC6.17 (3Q); also elsewhere on the board
LA21: ADR3.7, IC6.16 (4Q); also elsewhere on the board
LA22: ADR3.10, IC6.14 (6Q); also elsewhere on the board
LA23: ADR3.9, IC6.15 (5Q); also elsewhere on the board
LAR: CTRL.7, IC1.13 (7Q)
LCON: CTRL.9, IC1.15 (5Q)
LDR: CTRL.8, IC1.17 (3Q)
LFC0: IC14.16 (Y2), STATE.11
LFC1: IC14.14 (Y3), STATE.14
LFC2: IC15.18 (Y1), STATE.13
LHLT: IC15.5 (Y3), STATE.2
LIAC: IC14.7 (Y2), STATE.12
LLDS: IC15.14 (Y3), STATE.3
LMEM: CTRL.10, IC1.16 (4Q)
LR0: CTRL.1, IC1.19 (1Q)
LR1: CTRL.2, IC1.18 (2Q)
LR2: CTRL.4, IC1.12 (8Q)
LRD: IC15.3 (Y4), STATE.5
LRST: IC15.9 (Y1), STATE.1
LSP: CTRL.3, IC1.14 (6Q)
LSUP: IC14.3 (Y4), STATE.9
LSYN: IC15.16 (Y2), STATE.8
LUDS: IC15.12 (Y4), STATE.4
LUSR: IC14.5 (Y3), STATE.10
LWR: IC15.7 (Y2), IC15.17 (A4), STATE.6
unnamed: IC14.4 (A2), IC14.18 (Y1)
unnamed: IC14.9 (Y1), IC15.2 (A1)
unnamed: IC14.6 (A3), IC14.12 (Y4)
unnamed: !HALT.1, IC15.15 (A3), R1.2
R/!WB: IC15.13 (A2); also elsewhere on the board
VCC: IC1.20 (VCC), IC4.20 (VCC), IC5.20 (VCC), IC6.20 (VCC), IC14.20 (VCC), IC15.20 (VCC), R1.1; also elsewhere on the board

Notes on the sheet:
BOARD #2 USR/CPU ADDRESS LED CONTROL STATE & CONTROL LEDS
